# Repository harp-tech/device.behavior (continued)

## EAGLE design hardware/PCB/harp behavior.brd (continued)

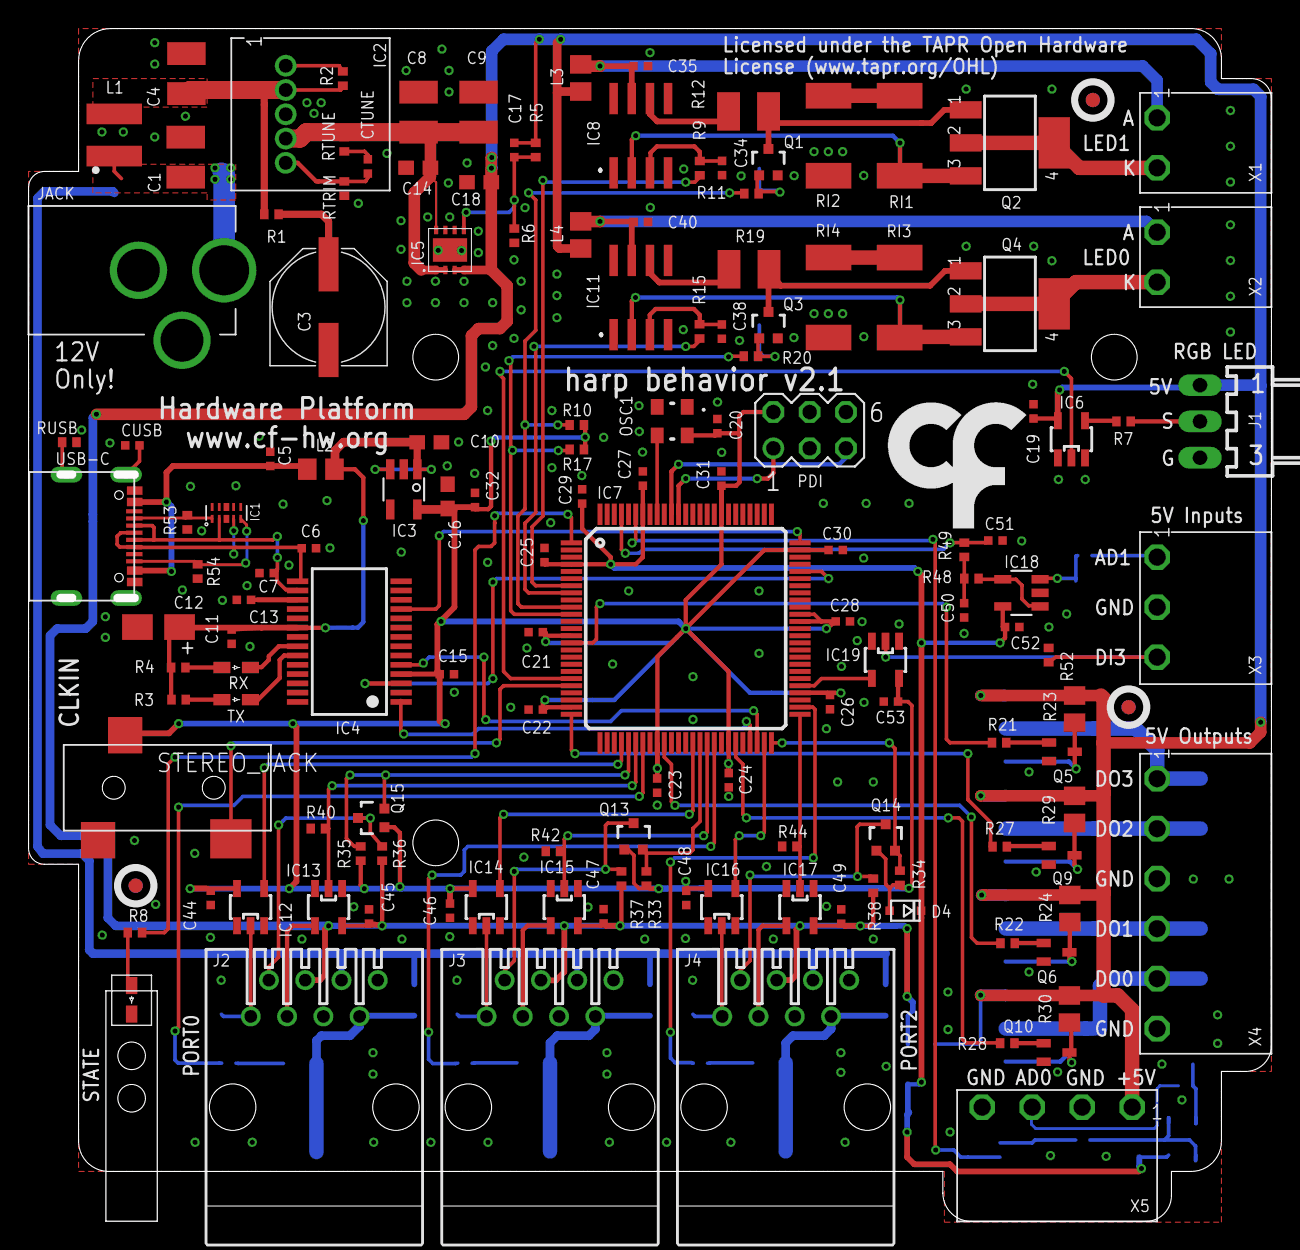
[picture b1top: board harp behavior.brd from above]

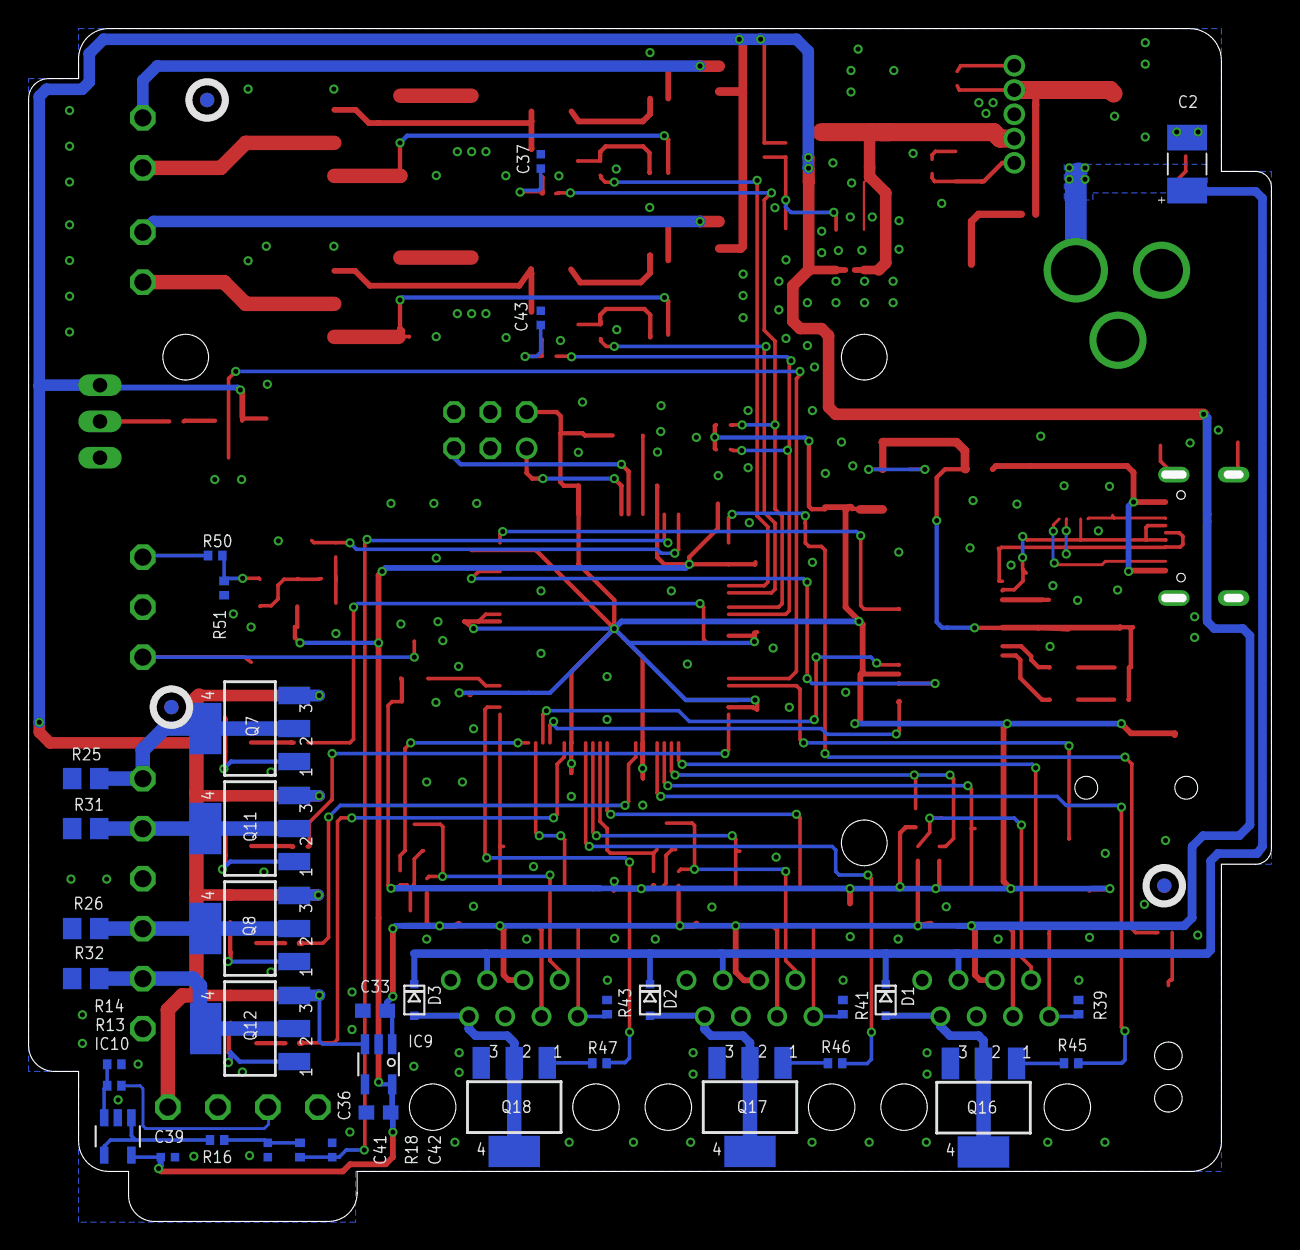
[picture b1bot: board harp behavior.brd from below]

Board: 2 copper layers, 86.4 x 82.9 mm, 186 parts (39 on the bottom side), 112 nets.

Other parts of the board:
U$1: LED_PIPE_7513D2-L
U$2, U$3, U$4, U$5, U$6, U$7: FIDUCIAL
U$9: LOGO_6

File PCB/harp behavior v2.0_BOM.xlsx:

| Part(s) | Quantity | Description | Distributor | Part. No.
 | IC1 | 1 | ESD Protection Low Cap | Mouser | 511-USBLC6-2SC6Y
 | IC2 | 1 | Conversores CC/CC sem isolação 12Vin, 0.591-6Vout 1.5A, Positive Logic | Mouser | 580-OKR-T/1.5-W12-C
 | IC3, IC9 | 2 | LDO 250mA Ultra-Lo Noise LDO Reg 3.3V | Mouser | 595-LP5907MFX-3.3NPB
 | IC4 | 1 | IC USB USB to Serial UART Enhanced IC SSOP-28 | Mouser | 895-FT232RL
 | IC5 | 1 | Reguladores de tensão de LDO Sgl Output LDO 1.5A Adj Lo Noise Hi PSRR | Mouser | 595-TPS78601DCQR
 | IC6, IC13, IC15, IC17 | 4 | Buffers e line drivers 1.65-5.5V Single Non-Inverting TTL | Mouser | 863-M74VHC1GT50DTT1G
 | IC7 | 1 | Microcontroladores de 8 bits - MCU 100TQFP, IND TEMP GREEN, 1.6-3.6V | Mouser | 556-ATXMEGA128A1U-AU
 | IC8, IC11 | 2 | Amplificadores de precisão 50MHz Low Distort Low Noise CMOS Prec | Mouser | 584-AD8651ARZ
 | IC10, IC18 | 2 | Amp Op 2.2V 50MHz Low Noise Single Supply | Mouser | 595-OPA365AIDBVR
 | IC12, IC14, IC16, IC19 | 4 | SingleBuffer / Driver, 1.65V to 5.5V, SOT-23-5 | Mouser | 595-SN74LVC1G125DBVR
 | Q1, Q3, Q13, Q14, Q15 | 5 | DMG1012UW MOSFET N Channel, 1 A, 20 V, 0.3 ohm, 4.5 V, 500 mV | Mouser | 621-DMG1012UW-7
 | Q2, Q4 | 2 | Bipolar (BJT) Single Transistor, NPN, 70 V, 150 MHz, 2 W, 2 A, 500 hFE | Mouser | 522-FZT692BTA
 | Q7, Q8, Q11, Q12 | 4 | MOSFET -60V 2.6A P-Channel SOT-223-4 | Mouser | 863-NTF2955T1G
 | Q5, Q6, Q9, Q10 | 4 | BJT NPN SURFACE MOUNT SMALL SIGNAL TRANS SOT-23-3 | Mouser | 621-BC817-40W-7
 | Q16, Q17, Q18 | 3 | MOSFET 60V 3A N-Channel SOT-223-3 | Mouser | 863-NTF3055L108T1G
 | D1, D2, D3, D4 | 4 | DIODE SCHOTTKY 30V 1A SOD323 | Mouser | 621-SDM100K30L-7
 | C17 | 1 | CAP CER 13pF 50V ±5% C0G 0402 | Mouser | 603-CC402JRNPO9BN130
 | C6, C7 | 2 | CAP CER 47pF 50V ±5% C0G 0402 | Mouser | 77-VJ0402A470JXACBC
 | CUSB | 1 | CAP CER 4.7nF 50V ±10% X7R 0402 | Mouser | 81-GCM155R71H472K37D
 | C41, C42, C50, C51 | 4 | CAP CER 15nF 16V ±10% X7R 0402 | Mouser | 581-0402YC153KAT2A
 | C5, C11, C13, C15, C19, C20, C21, C22, C23, C24, C25, C26, C27, C28, C30, C31, 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 | 29 | CAP CER 100nF 10V ±10% X5R 0402 | Farnell | 2310530
 | C29, C32 | 2 | CAP CER 330nF 10V ±10% X5R 0402 | Digikey | CL05A334KP5NNNC
 | C12 | 1 | CAP TAN 4.7uF 10V ±10% 1206 | Mouser | 80-T491A475K107280
 | C10, C14, C16, C18, C33, C36 | 6 | CAP CER 10uF 35V ±20% X5R 0603 | Mouser | 81-GRM188R6YA106MA3D
 | C2 | 1 | CAP TAN 22uF 20V ±20% 1210 | Mouser | 667-20TQC22MYFB
 | C1, C4 | 2 | CAP CER 22uF 25V ±20% X7R 1210 | Mouser | 81-GRM32ER71E226ME5K
 | C8, C9 | 2 | CAP CER 47uF 16V ±10% X6S 1210 | Mouser | 81-GRM32EC81C476KE5K
 | C3 | 1 | CAP ELE 100uF 25V ±20% E7 | Mouser | 667-25SVF100M
 | R1, R9, R15 | 3 | RES SMD 0Ω ±5% 0402 | Mouser | 667-ERJ-2GE0R00X
 | RI1, RI2, RI3, RI4 | 4 | RES SMD 4.99Ω ±1% 2512 1W | Mouser | 71-CRCW25124R99FNEG
 | R8 | 1 | RES SMD 68Ω ±5% 0402 | Mouser | 667-ERJ-2GEJ680X
 | R7, R11, R20 | 3 | RES SMD 100Ω ±1% 0402 | Mouser | 667-ERJ-2RKF1000X
 | R12, R19 | 2 | RES SMD 200Ω ±5% 1210 0.5W | Mouser | 71-CRCW1210J-200-E3
 | RTRIM | 1 | RES SMD 243Ω ±1% 0402 | Mouser | 667-ERJ-2RKF2430X
 | R45, R46, R47 | 3 | RES SMD 330Ω ±1% 0402 | Mouser | 667-ERJ-PA2F3300X
 | R16, R18, R21, R22, R27, R28, R33, R34, R35, R36, R37, R38, R48, R49 | 14 | RES SMD 10kΩ ±1% 0402 | Farnell | 2130433
 | R23, R24, R25, R26, R29, R30, R31, R32 | 8 | RES SMD 549Ω ±1% 0805 | Mouser | 667-ERJ-6ENF5490V
 | R14, R51 | 2 | RES SMD 15kΩ ±1% 0402 | Mouser | 667-ERJ-2RKF1502X
 | R13, R50 | 2 | RES SMD 24kΩ ±1% 0402 | Mouser | 667-ERJ-2RKF2402X
 | R6 | 1 | RES SMD 30.9kΩ ±1% 0402 | Mouser | 667-ERJ-2RKF3092X
 | R5 | 1 | RES SMD 95.3kΩ ±1% 0402 | Mouser | 667-ERJ-2RKF9532X
 | R10, R17, R39, R40, R41, R42, R43, R44, R52 | 9 | RES SMD 100kΩ ±1% 0402 | Mouser | 667-ERJ-2RKF1003X
 | RUSB | 1 | RES SMD 1MΩ ±1% 0402 | Mouser | ERJ-2RKF1004X
 | L1 | 1 | Indutores fixos LPS4012 Low Profile 1.5uH 2.2A 20% SMD | Mouser | 994-LPS4012-152MRB
 | L2 | 1 | Esferas de ferrite 40ohms 100MHz 1.5A Monolithic 0805 SMD | Mouser | 875-MI0805K400R-10
 | L3, L4 | 2 | Esferas de ferrite 600ohms 100MHz .5A Monolithic 0805 SMD | Mouser | 875-HZ0805E601R-10
 | STATE | 1 | SMD Pure Green 20mA 0603 | Mouser | 78-TLMP1100-GS08
 | OSC1 | 1 | Oscillator, Low Power, -40C-85C, 10ppm | Mouser | 998-1001CI5032.0000T
 | CLKIN | 1 | CONN JACK STEREO 3.5MM SMD R/A | Digikey | SC1489-1-ND
 | PDI | 1 | CONN HEADER 6POS .100 STR 15AU | Digikey | 609-3210-ND
 | J2, J3, J4 | 3 | Modular Connector, RJ45, Jack, 8 Contacts, 8 Ways, 215877 Series, Cat3 | Mouser | 571-2158771
 |  | 3 | Ethernet Cable, Patch Lead, Cat5e, RJ45 Plug to RJ45 Plug, Beige, 500 mm | Farnell | 1526101
 | USB | 1 | Conectores USB MINI B RECEPT RA TH W/POST | Mouser | UX60-MB-5S8(70)
 | USB Cable | 1 | USB Cables / IEEE 1394 Cables USB A - MINI-B 1.5M - MINI-B 1.5M BLACK | Mouser | 88732-8702
 |  | 1 | LIGHT PIPE SGL RT ANGLE 3.6MM | Digikey | L71537-ND
 | JACK | 1 | Conectores de alimentação CC PCB 2.1MM | Mouser | 163-179PH-EX
 | WALL ADAPTER | 1 | AC/DC WALL MOUNT ADAPTER 12V 12W | Mouser | VER12US120-JA
 | J1 | 1 | Connector, Right Angle, 2.54 mm, 3 Contacts, Header, KK 254 7395 Series, TH | Farnell | 22-12-4032
 |  | 2 | Pluggable Terminal Block, 3.5 mm, 2 Ways, 28 AWG, 16 AWG, 1.5 mm², Screw | Mouser | TBP03P3-350-02GR
 |  | 1 | Pluggable Terminal Block, 3.5 mm, 3 Ways, 28 AWG, 16 AWG, 1.5 mm², Screw | Farnell | 20.1550M/3-E
 |  | 2 | Pluggable Terminal Block, 3.5 mm, 6 Ways, 28 AWG, 16 AWG, 1.5 mm², Screw | Mouser | TBP03P3-350-06GR
 |  | 1 | Pluggable Terminal Block, 3.5 mm, 4 Ways, 28 AWG, 16 AWG, 1.5 mm², Screw | Farnell | 20.1550M/4-E
 | X1, X2 | 2 | Terminal Block, Header, 3.5 mm, 2 Ways, 10 A, 250 V, Through Hole Right Angle | Mouser | TBP03R1-350-02GR
 | X3 | 1 | Terminal Block, Header, 3.5 mm, 3 Ways, 10 A, 250 V, Through Hole Right Angle | Farnell | 20.155MH/3-E
 | X4 | 1 | Terminal Block, Header, 3.5 mm, 6 Ways, 10 A, 250 V, Through Hole Right Angle | Mouser | TBP03R1-350-06GR
 | X5 | 1 | Terminal Block, Header, 3.5 mm, 4 Ways, 10 A, 250 V, Through Hole Right Angle | Farnell | 20.155MH/4-E
 |  | 8 | Nut, Hex, M3, 5.5mm Nylon | RS | 525-701
 |  | 4 | Machine Screw, M3, 10 mm, Nylon (Polyamide), Pan Head Slotted | RS | 185-4447
 | Components | 191
 | Licensed under the TAPR Open Hardware License (www.tapr.org/OHL)
 | Copyright 2017-2022 Artur Silva and Filipe Carvalho
 | Licensed under the TAPR Open Hardware License (www.tapr.org/OHL)
 | Copyright 2017 Artur Silva and Filipe Carvalho

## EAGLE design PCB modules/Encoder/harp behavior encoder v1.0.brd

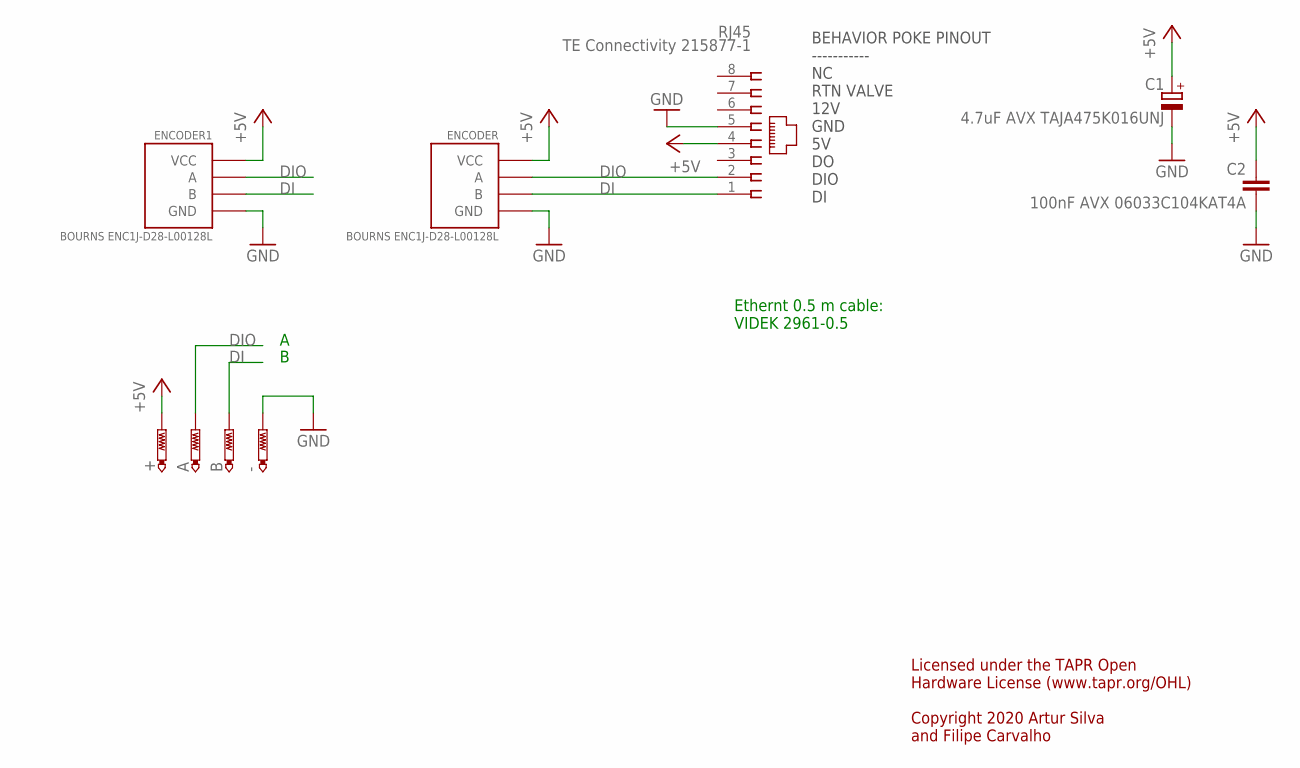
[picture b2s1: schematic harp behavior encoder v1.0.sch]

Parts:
+: PTR1PAD1-13; P1-13
-: PTR1PAD1-13; P1-13
A: PTR1PAD1-13; P1-13
B: PTR1PAD1-13; P1-13
C1: 4.7uF AVX TAJA475K016UNJ; A/3216-18W
C2: 100nF AVX 06033C104KAT4A; C0603
ENCODER, ENCODER1: BOURNS ENC1J-D28-L00128L; STYLEC
RJ45: TE Connectivity 215877-1; 520426-4

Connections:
+5V: +.TP, C1.+, C2.1, ENCODER.+ (VCC), ENCODER1.+ (VCC), RJ45.4
DI: B.TP, ENCODER.B, ENCODER1.B, RJ45.1
DIO: A.TP, ENCODER.A, ENCODER1.A, RJ45.2
GND: -.TP, C1.-, C2.2, ENCODER.- (GND), ENCODER1.- (GND), RJ45.5

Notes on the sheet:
Licensed under the TAPR Open Hardware License (www.tapr.org/OHL) Copyright 2020 Artur Silva and Filipe Carvalho
BEHAVIOR POKE PINOUT ----------- NC RTN VALVE 12V GND 5V DO DIO DI
Ethernt 0.5 m cable: VIDEK 2961-0.5

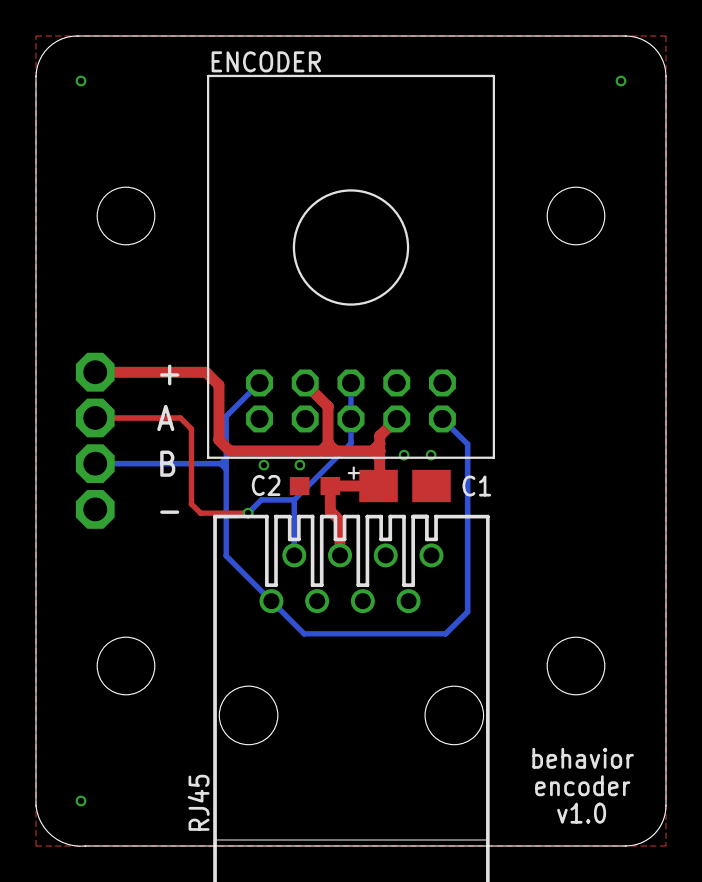
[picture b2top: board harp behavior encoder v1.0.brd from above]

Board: 2 copper layers, 35.0 x 45.0 mm, 9 parts (1 on the bottom side), 4 nets.

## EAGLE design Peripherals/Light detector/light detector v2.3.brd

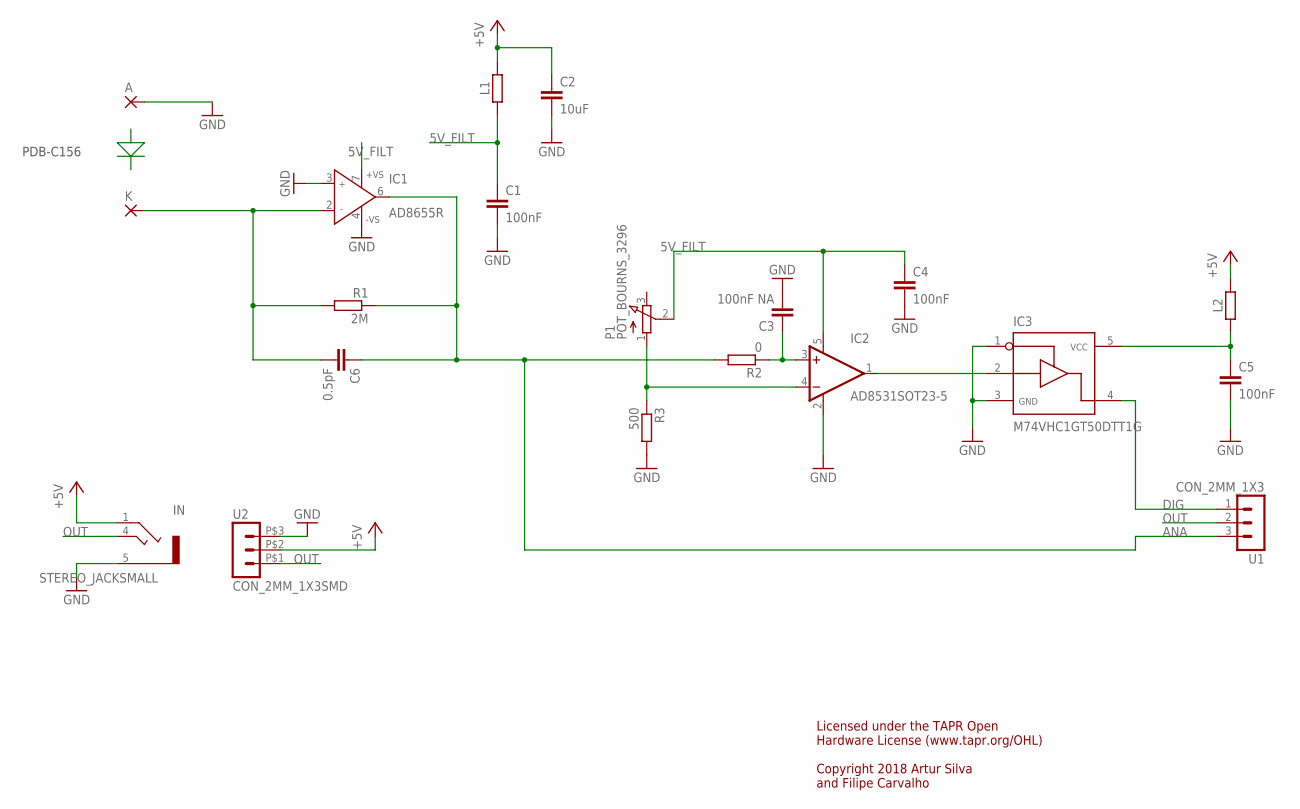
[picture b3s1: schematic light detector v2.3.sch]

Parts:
A: 1,6/0,8
C1, C4, C5: 100nF; C0402
C2: 10uF; C0603
C3: 100nF NA; C0402
C6: 0.5pF; C0402
IC1: AD8655R; SO8
IC2: AD8531SOT23-5; SOT23-5
IC3: M74VHC1GT50DTT1G; SOT23-5
IN: STEREO_JACKSMALL; 35RASMT2BHNTRX_
K: 1,6/0,8
L1, L2: 1k@100M; R0402
P1: POT_BOURNS_3296; POT_BOURNS_3296P
R1: 2M; R0402
R2: 0; R0402
R3: 500; R0402
U1: CON_2MM_1X3
U2: CON_2MM_1X3SMD; CON_2MM_1X3_SMD

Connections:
5V_FILT: C1.1, C4.1, IC1.7 (+VS), IC2.5 (V+), L1.2, P1.2 (S)
+5V: C2.1, IN.1, L1.1, L2.2, U2.P$2 (2)
ANA: C6.1, IC1.6 (OUT), R1.1, R2.2, U1.3
DIG: IC3.4, U1.1
GND: A.1, C1.2, C2.2, C3.2, C4.2, C5.2, IC1.3 (IN+), IC1.4 (-VS), IC2.2 (V-), IC3.1, IC3.3, IN.5, R3.2, U2.P$3 (3)
IN2: IC2.4 (-IN), P1.1 (A), R3.1
unnamed: C6.2, IC1.2 (IN-), K.1, R1.2
unnamed: C3.1, IC2.3 (+IN), R2.1
unnamed: IC2.1 (OUT), IC3.2
unnamed: C5.1, IC3.5, L2.1
OUT: IN.4, U1.2, U2.P$1 (1)

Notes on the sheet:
Licensed under the TAPR Open Hardware License (www.tapr.org/OHL) Copyright 2018 Artur Silva and Filipe Carvalho
PDB-C156

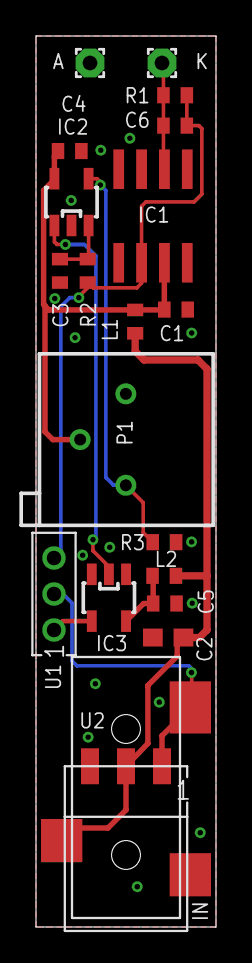
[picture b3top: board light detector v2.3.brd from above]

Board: 2 copper layers, 10.0 x 49.5 mm, 21 parts (1 on the bottom side), 11 nets.

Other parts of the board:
U$2: LOGO_8

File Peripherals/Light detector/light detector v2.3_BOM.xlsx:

| Part(s) | Quantity | Description | Distributor | Part. No.
 | IC1 | 1 | IC OPAMP GP 28MHZ RRO 8SOIC | Digikey | AD8655ARZ-REEL7CT-ND
 | IC2 | 1 | IC OPAMP GP 3MHZ RRO SC70-5 | Digikey | AD8531ARTZ-REEL7
 | IC3 | 1 | Buffers e line drivers 1.65-5.5V Single Non-Inverting TTL | Digikey | M74VHC1GT50DTT1GOSCT-ND
 | P1 | 1 | TRIMMER 20K OHM 0.5W PC PIN | Digikey | 3296P-203LF-ND
 | R2 | 1 | RES SMD 0 OHM JUMPER 1/10W 0402 | Digikey | P0.0JCT-ND
 | R3 | 1 | RES SMD 499 OHM 1% 1/10W 0402 | Digikey | P499LCT-ND
 | R1 | 1 | RES SMD 2000K OHM 1% 1/10W 0402 | Digikey | ERJ-2GEJ205X
 | C6 | 1 | CAP CER 0.5PF 50V C0G/NP0 0402 | Digikey | 490-6264-1-ND
 | C1, C4, C5 | 3 | CAP CER 100nF 10V X5R 0402 | REEL | REEL
 | C2 | 1 | CAP CER 10uF 10V ±10% X5R 0603 | Digikey | 490-10474-1-ND
 | L1, L2 | 2 | FERRITE BEAD 1 KOHM 0402 1LN | Digikey | 445-2163-1-ND
 | U1 | 1 | CONN HEADER R/A 3POS 2MM | Digikey | M22-2030305
 | U2 | 0 | CONN RCPT 2MM SMD 3POS | Digikey | 952-3182-2-ND
 | Jumper | 1 | CONN JUMPER SHORTING GOLD BLACK | Digikey | M22-1900005
 | IN | 1 | SMT 3.5 STEREO REEL | Digikey | 502-35RASMT2BHNTRX
 |  | 1 | CABLE 3.5MM STEREO PLUG W/WIRES | Digikey | 1847-BC-A3ML006F-ND
 | Sensor | 1 | PHOTODIODE BLUE 8.02MM SQ CLEAR | Digikey | PDB-C156-ND
 | Components | 19
 | Licensed under the TAPR Open Hardware License (www.tapr.org/OHL)
 | Copyright 2018 Artur Silva and Filipe Carvalho

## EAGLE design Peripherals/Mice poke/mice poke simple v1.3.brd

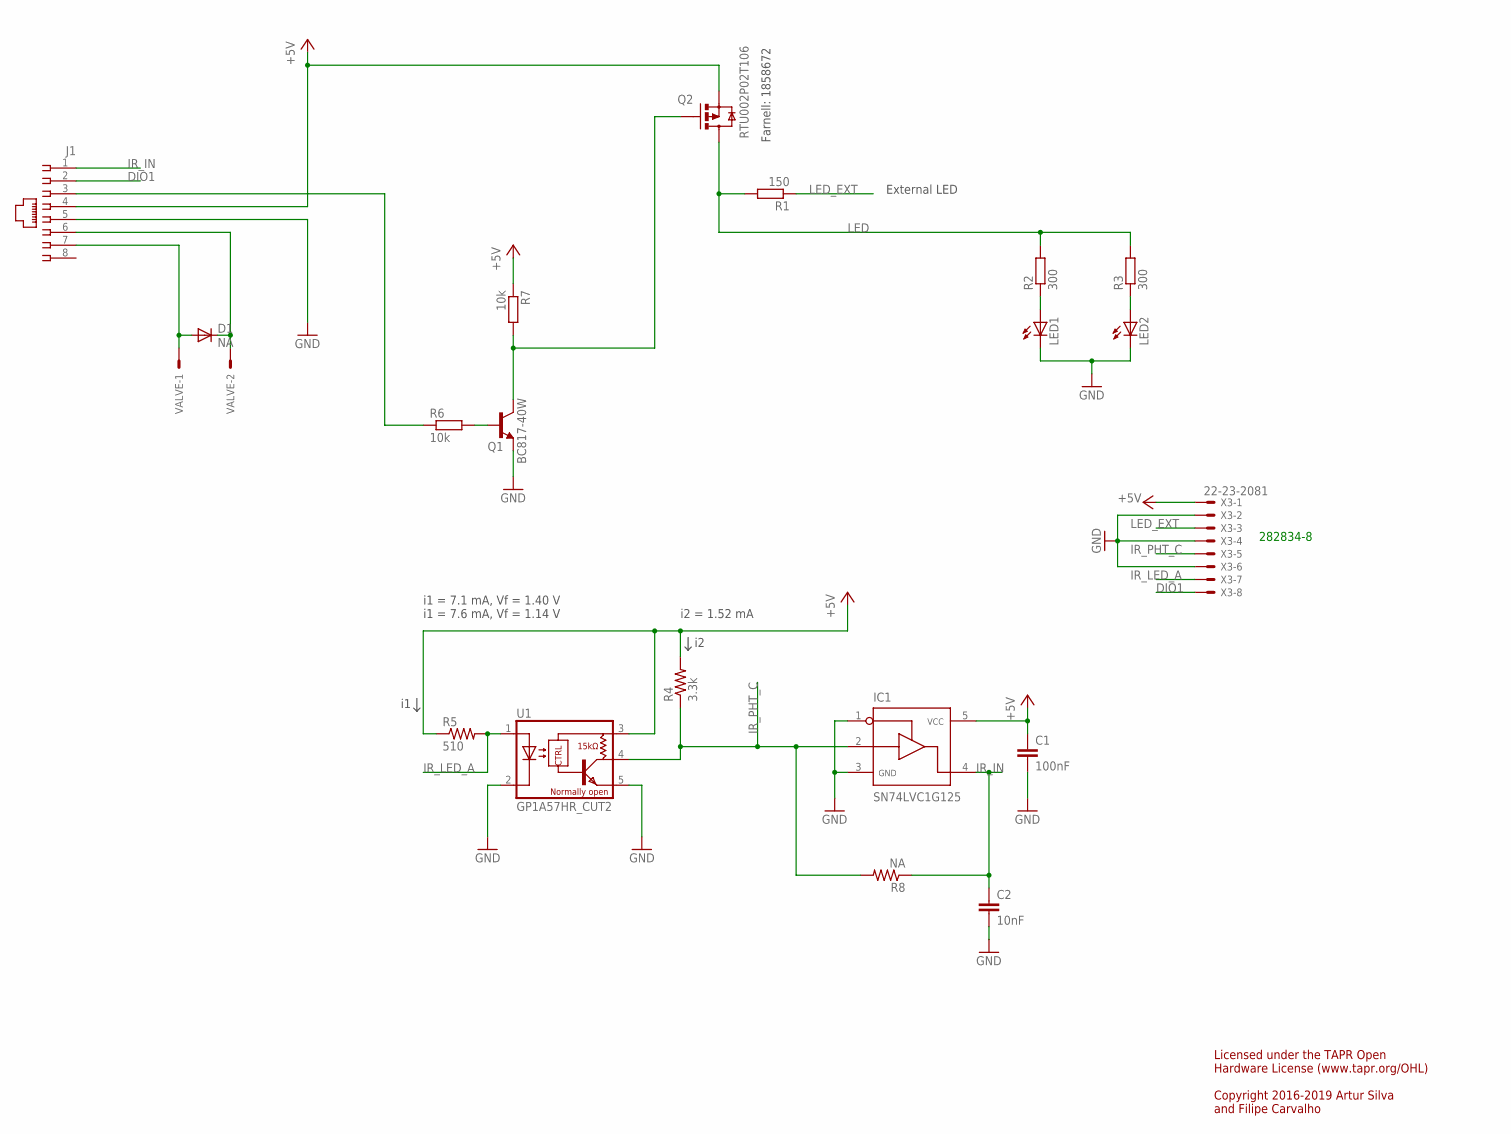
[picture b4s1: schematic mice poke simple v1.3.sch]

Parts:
C1: 100nF; C0402
C2: 10nF; C0402
D1: NA; SOD323-R
IC1: SN74LVC1G125; SOT23-5
J1: 215878-2
LED1, LED2: LED3MM
Q1: BC817-40W; SOT323-BEC
Q2: RTU002P02T106; SOT323
R1: 150; R0402
R2, R3: 300; R0402
R4: 3.3k; R0402
R5: 510; R0402
R6, R7: 10k; R0402
R8: NA; R0402
U1: GP1A57HR_CUT2
VALVE: 22-23-2021
X3: 22-23-2081

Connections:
+5V: C1.1, IC1.5, J1.4, Q2.1 (S), R4.2, R5.1, R7.1, U1.3 (VCC), X3.1
DIO1: J1.2, X3.8
GND: C1.2, C2.2, IC1.1, IC1.3, J1.5, LED1.K (C), LED2.K (C), Q1.E, U1.2 (C), U1.5 (GND), X3.2, X3.4, X3.6
IR_IN: C2.1, IC1.4, J1.1, R8.1
IR_LED_A: R5.2, U1.1 (A), X3.7
IR_PHT_C: IC1.2, R4.1, R8.2, U1.4 (VO), X3.5
LED: Q2.3 (D), R1.2, R2.2, R3.2
LED_EXT: R1.1, X3.3
unnamed: D1.A, J1.7, VALVE.1
unnamed: D1.C, J1.6, VALVE.2
unnamed: J1.3, R6.1
unnamed: LED2.A, R3.1
unnamed: LED1.A, R2.1
unnamed: Q1.C, Q2.2 (G), R7.2
unnamed: Q1.B, R6.2

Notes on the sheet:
i1 = 7.1 mA, Vf = 1.40 V i1 = 7.6 mA, Vf = 1.14 V
i2 = 1.52 mA
External LED
Farnell: 1858672
Licensed under the TAPR Open Hardware License (www.tapr.org/OHL) Copyright 2016-2019 Artur Silva and Filipe Carvalho
282834-8

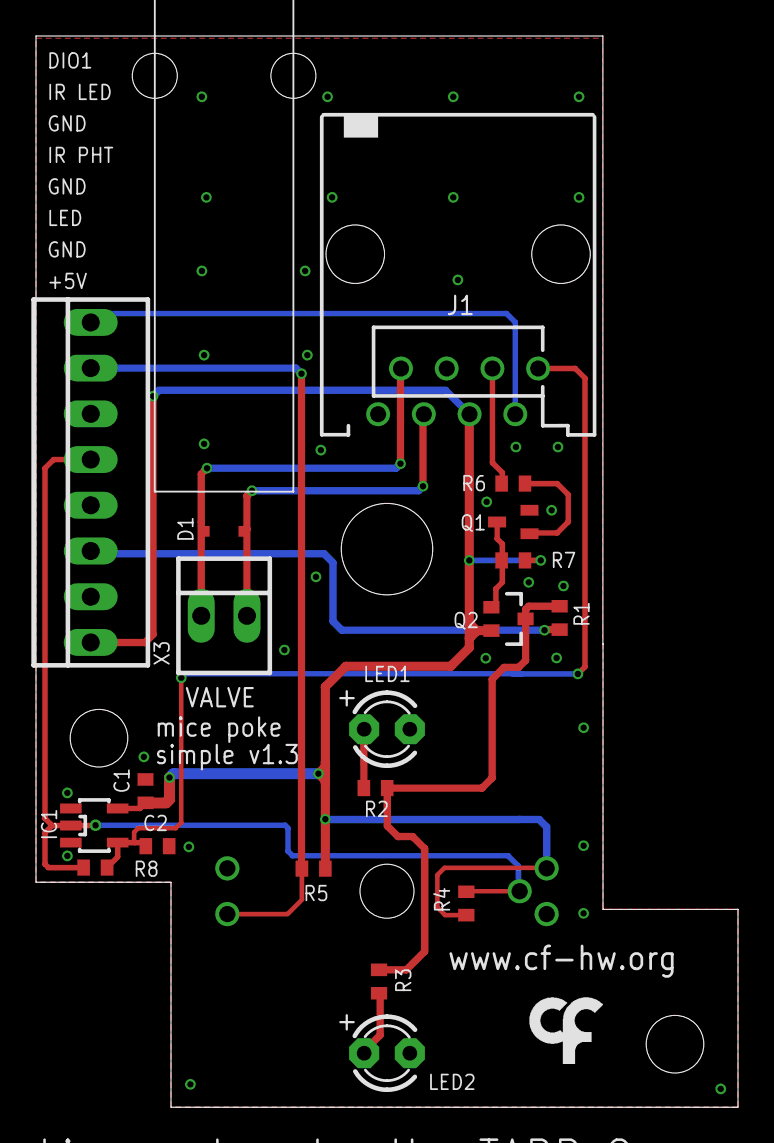
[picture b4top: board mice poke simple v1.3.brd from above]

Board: 2 copper layers, 39.0 x 59.5 mm, 21 parts (1 on the bottom side), 15 nets.

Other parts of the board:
U$2: LOGO_7

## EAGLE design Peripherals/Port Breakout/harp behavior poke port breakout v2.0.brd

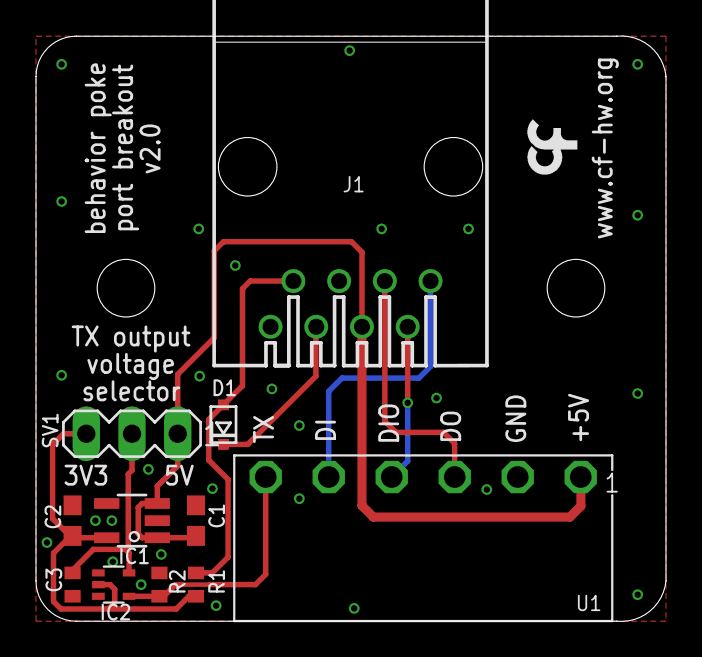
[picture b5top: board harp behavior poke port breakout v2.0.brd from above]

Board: 2 copper layers, 35.0 x 32.5 mm, 12 parts (0 on the bottom side), 10 nets.

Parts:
C1, C2: 4.7uF; C0603
C3: 100nF; C0402
D1: SOD-323-DIODE
IC1: TLV70033DDCR; TSOT23-5
IC2: 74AHC1G04DCK; SC70-5
J1: Port 1; 520426-4
R1: 1k; R0402
R2: 100k; R0402
SV1: MA03-1
U1: CON_3.5MM_1X6
U$2: LOGO_8

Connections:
+3V3: C2.1, IC1.5, IC2.2, R1.1, SV1.3
+5V: C1.1, IC1.1, IC1.3, J1.4, SV1.1, U1.P1
+12V: D1.C, J1.6
DI: J1.1, U1.P5
DIO: J1.2, U1.P4
DO: J1.3, U1.P3
GND: C1.2, C2.2, C3.1, IC1.2, IC2.3, J1.5, R2.2, U1.P2
unnamed: C3.2, IC2.5, SV1.2
SUP_RTN: D1.A, J1.7, R1.2
TX: IC2.4, R2.1, U1.P6

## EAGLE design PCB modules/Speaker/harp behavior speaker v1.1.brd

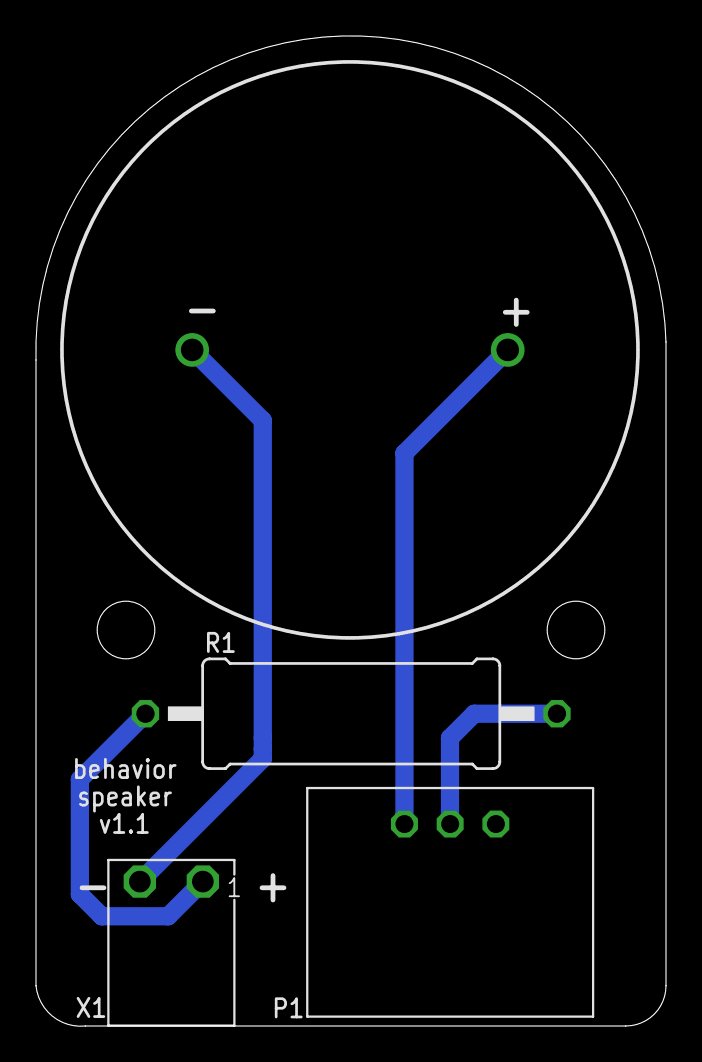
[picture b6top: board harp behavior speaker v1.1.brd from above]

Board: 2 copper layers, 35.0 x 55.0 mm, 3 parts (0 on the bottom side), 2 nets.

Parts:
P1: 91A1A-B28; MODEL91
R1: 24; 0617/22
X1: CON_3.5MM_1X2

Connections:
unnamed: R1.1, X1.P1
unnamed: P1.P$2, R1.2

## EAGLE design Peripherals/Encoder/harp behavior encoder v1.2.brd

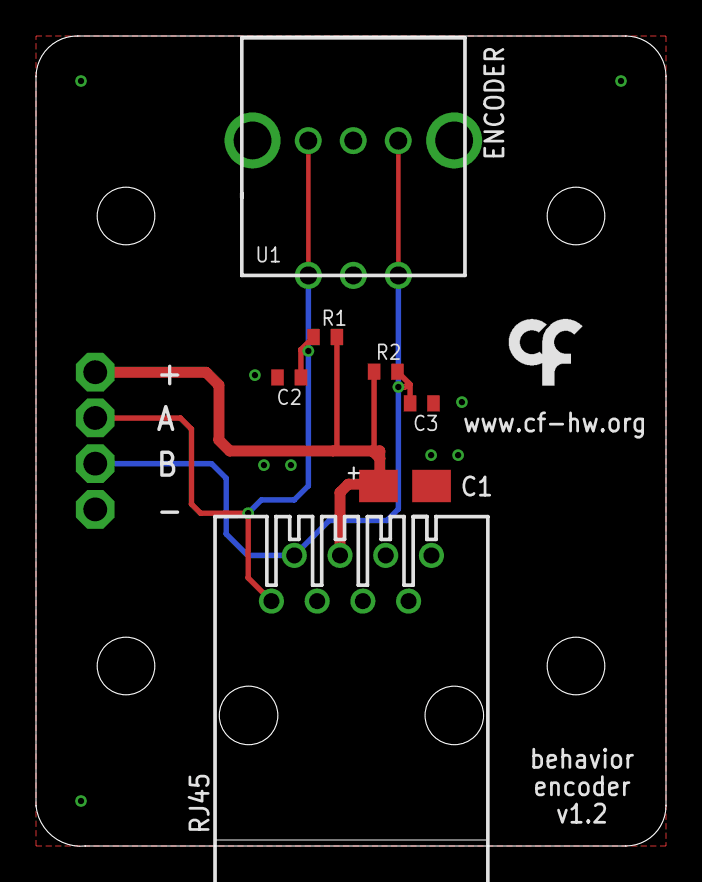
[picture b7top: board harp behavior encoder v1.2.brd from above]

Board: 2 copper layers, 35.0 x 45.0 mm, 12 parts (0 on the bottom side), 4 nets.

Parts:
+: PTR1PAD1-13; P1-13
-: PTR1PAD1-13; P1-13
A: PTR1PAD1-13; P1-13
B: PTR1PAD1-13; P1-13
C1: 4.7uF AVX TAJA475K016UNJ; A/3216-18W
C2, C3: 100nF; C0402
R1, R2: 10k; R0402
RJ45: TE Connectivity 215877-1; 520426-4
U1: ENCODER_EC12
U$3: LOGO_7

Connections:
+5V: +.TP, C1.+, R1.1, R2.1, RJ45.4
DI: A.TP, C2.1, R1.2, RJ45.1, U1.A
DIO: B.TP, C3.1, R2.2, RJ45.2, U1.B
GND: -.TP, C1.-, C2.2, C3.2, RJ45.5, U1.C

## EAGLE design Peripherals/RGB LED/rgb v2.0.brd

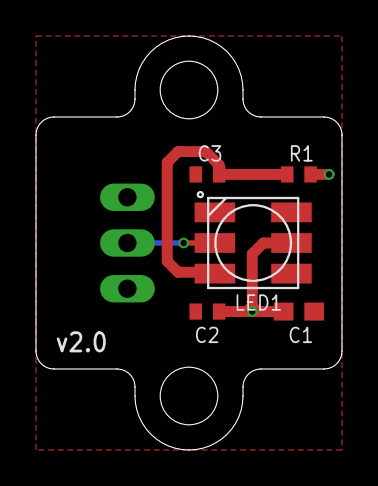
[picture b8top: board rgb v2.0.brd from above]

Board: 2 copper layers, 17.0 x 23.0 mm, 6 parts (1 on the bottom side), 4 nets.

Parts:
C1: 10uF; C0603
C2, C3: 100nF; C0402
J1: 22-05-7038-03; 7395-03
LED1: WS2812LARGER; WS2812_LARGER
R1: 33; R0402

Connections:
+5V: C1.1, C2.1, J1.1, LED1.LEDVDD, R1.2
GND: C1.2, C2.2, C3.2, J1.3, LED1.VSS
unnamed: C3.1, LED1.VDD, R1.1
SERIAL_LED0: J1.2, LED1.DI

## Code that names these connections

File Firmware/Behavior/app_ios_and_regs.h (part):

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/* Registers' address                                                   */
/************************************************************************/
/* Registers */
#define ADD_REG_PORT_DIS                    32 // U8     Reflects the state of DI digital lines of each Port
#define ADD_REG_RESERVED0                   33 // U8     Reserved for future use
#define ADD_REG_OUTPUTS_SET                 34 // U16    Set the correspondent output
#define ADD_REG_OUTPUTS_CLEAR               35 // U16    Clear the correspondent output
#define ADD_REG_OUTPUTS_TOGGLE              36 // U16    Toggle the correspondent output
#define ADD_REG_OUTPUTS_OUT                 37 // U16    Control the correspondent output
#define ADD_REG_PORT_DIOS_SET               38 // U8     Set the correspondent DIO
#define ADD_REG_PORT_DIOS_CLEAR             39 // U8     Clear the correspondent DIO
#define ADD_REG_PORT_DIOS_TOGGLE            40 // U8     Toggle the correspondent DIO
#define ADD_REG_PORT_DIOS_OUT               41 // U8     Control the correspondent DIO
#define ADD_REG_PORT_DIOS_CONF              42 // U8     Set the DIOs direction (1 is output)
#define ADD_REG_PORT_DIOS_IN                43 // U8     State of the DIOs
#define ADD_REG_DATA                        44 // I16[2] Voltage at ADC input and decoder (poke 2) value
#define REG_DATA_INDEX_ADC0						0	// Index for the value of ADC0
#define REG_DATA_INDEX_ADC1						1   // Index for the value of ADC1
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#define MSK_MIMIC                          0x0F         // 
#define GM_MIMIC_NONE                      0x00         // 
#define GM_MIMIC_DIO0                      0x01         // Is reflected on DIO0
#define GM_MIMIC_DIO1                      0x02         // Is reflected on DIO1
#define GM_MIMIC_DIO2                      0x03         // Is reflected on DIO2
#define GM_MIMIC_DO0                       0x04         // Is reflected on DO0
#define GM_MIMIC_DO1                       0x05         // Is reflected on DO1
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
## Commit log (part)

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2017-11-24 Added hability to change the DOx frquency and Duty Cycle when already operating the DOx outputs.
2017-11-24 Negated LEDs transistor drive and added new bit to be used on register PWM_START.
2017-11-24 Added pulse functionality and clean some registers.
2017-11-24 Added pulse functionality, shutdown in case of error, correct DAC initialization, changed some register defaults and added some register initializations.
2017-11-24 Minor changes on file registers.xls.
2017-11-25 Removed unnecessary library.
2017-11-25 Fixed the ADC conversion.
2017-11-25 Increased ADC stabilization time before measuring offset from 5 us to 100 us (doesn't have impact on the offset value).
2017-11-26 Improved RGB control, changed RGB defaults and clean up code.
2018-01-11 Fixed #1.
2018-01-11 Updated to Atxmega Harp core version 1.1.
2018-01-11 Increased firmware version to 1.1
2018-01-12 Updated hwbp_app_initialize function to make it easy for the releases.
2018-01-17 Fixed Rgbs issue where the high level interrupts were interrupting the RGB bus and creating erroneous colors. Note: Not sure if completely fixed -- the Clock Sync's uart can still create interruption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
2018-01-17 Added code to keep the register OUTPUTS_OUT constantly updated.
2018-01-29 Updated to Atxmega Harp core version 1.3.
2018-01-31 Updated to Atxmega Harp core version 1.4.
2018-02-23 Added new registers and implemented quadrature encoder register's code.
2018-02-23 Increased firmware version to 2.0.
2018-03-01 Implemented 3 new features (camera controller, quadrature counter, servo motor controller) and renamed/removed some registers.
2018-03-02 Deleted the register DIS_ENCODERS.
2018-03-02 Fixed issue that was creating a bad frequency when updating the frequency registeres during PWM execution.
2018-03-02 Fixed issue. The stop pwm of channel 1, 2 and 3 was not operational.
2018-03-02 Fixed issue that was turning the cameras off after the pulse period.
2018-03-04 Reordered the GRB array of colors to RGB.
2018-03-04 Increased lower limit of the camera frequency to 2 Hz (1 Hz was not working properly).
2018-03-04 Corrected return values when writing to some registers.
2018-03-04 Ability to update the quadrature counter value.
2018-03-04 Added new feature: servo motor is enabled when the pwm pulse registers are updated.
2018-03-04 Updated the registers default list.
2018-03-04 Removed old ADC register from the default values list.
2018-03-14 Corrected issue: when stopping the camera triggering, the last pulse was not correct.
2018-03-14 Increased firmware version to 2.1.
2018-04-27 Added filter to the PORTx digital inputs.
2018-04-27 Increased firmware version to 2.2.
2018-12-14 Reduced analog input conversion to 1 KHz.
2019-01-03 Updated hardware version to the latest version available.
2019-01-03 Updated firmware version to 2.3. Needed to overcome some preliminary versions 2.2 released for tests..
2019-01-10 Correct events from cameras triggering.
2019-02-06 Updated to core version 1.5 and use new ADC routines for the analog reading.
2019-02-11 Updated to core version 1.6.
2019-12-04 Added ability to mimic the infrared beams and valves into the outputs.
2020-05-24 Added fabrication files.
2021-11-03 Added license files
2022-01-22 Implemented a low-pass filter for the Pokes' digital input
2022-01-22 Increased firmware version
2022-03-17 Upadate registers.xls with new input filter register and update metadata
2022-03-17 Add low pass filter register missing on app_funcs.h from previous release (v2.6)
2022-03-17 Configure pokes DIOs as inputs, add respective events and increase version
2022-03-17 Correct hw version of release v2.6 file and add release v2.5
2022-03-17 Update project version to v7.0 and add v6.2 compatible version files
2022-05-20 Updated to harp core v1.10
2022-05-20 Added ability to calculate ADC offset and read ADC1.
    The devices is now able to calculate its own ADC offset and apply it to ADC readings.
    ADC readings are now handled by interrupts.
    Reading of ADC1 is done for hardware version 2.0.
2022-05-21 Updated LICENSE date.
2022-05-26 Implemented digital input DI3 on firmware.
2022-07-01 Harp behavior v2.0 hardware CAD files
2022-07-01 Revert "Harp behavior v2.0 hardware CAD files"
    This reverts commit b7fb75ff22a1f2c396da8856b179b4330b59d1a1.
2022-07-06 Added firmware image files.
2022-08-04 Added fw release 2.7 .hex file
2022-08-30 Updated README.md.
2022-09-13 Added a new event, when the last trigger is sent to the camera.
2022-09-16 Correct files added
2022-09-16 Organize folders and add peripheral boards
2022-09-16 License files added
2022-09-21 Organized files for PCB version 1.2.
2022-09-21 Added the available peripherals.
2022-09-21 Added PCB version 2.0.
2022-09-22 Added device's photo.
2022-10-05 Added port breakout v2.0.
2022-10-05 Minor corrections.
2022-10-05 Added production files.
2022-11-25 Added port breakout v2.1.
2022-11-30 Added BOM for v2.0 and updated CONTRIB file
2022-12-09 Updated port breakout v2.1
2022-12-23 refactor repository structure
2022-12-27 Added specific .gitignore for Hardware.
2022-12-27 Organized files for PCB version 2.0.
2022-12-27 Removed Releases folder from Firmware.
    Firmware will be found under repository releases from now on.
2022-12-27 Added specific .gitignore for Firmware.
2022-12-27 Created registers and control bits.
2022-12-27 Implemented the new functionality.
    Implements the ability to send the current timestamp over serial on Port 2, using the Valve line.
2022-12-27 Released fw 3.1 with atxmega harp core 1.11
2023-01-25 Correct mechanical version v1.x
2023-01-25 Add mechanical files v2.0 and License
2023-03-23 Add prototype device schema and interface
2023-03-27 Regenerate high-level device interface
2023-03-28 Add interface license and fix description
2023-03-29 Generate symbols package
2023-06-06 Add second ADC channel to schema
2023-06-06 Update `Device` class to the new schema
2023-06-06 Increment patch version
2023-06-07 Change AnalogData payloadSpec name
2023-06-07 Update `Device` class
2023-06-28 Fix register mask reference
2023-06-28 Refactor DigitalInput register naming
2023-07-31 Update interface to use new generators
2023-08-03 Add missing package metadata for stable release
2023-08-10 Updated versions.
2023-08-10 Replaced harp core 1.11 with 1.13.
2023-08-31 Raised version.
2023-08-31 Created new register EncoderMode.
2023-08-31 Implemented the functionality.
2023-08-31 Fixed core initialization.
2023-08-31 Added register description.
2023-09-06 Adding register limits
2023-09-18 Change encoder mode register and mask name
2023-11-19 Update interface to emit new encoder mode register
2023-11-19 Update interface to emit private registers
2024-04-18 Include device metadata file as embedded resource
2024-04-18 Add operator to retrieve embedded device metadata
2024-05-02 Document `Event` access for CameraStop register
2024-05-06 Document Event feature
2024-09-29 Fix register access description
2024-11-01 Update default launch settings
2024-11-07 Update generators to use embedded device metadata
2024-11-09 Add library package type to interface project
2024-11-16 Add CI to check for uncommitted changes during the regeneration process
2025-02-01 Add operator to convert raw adc units to volt
2025-02-01 Fix adc to voltage conversion
2025-02-01 Fix minor typo
2025-05-24 Update interface using new generators
2025-05-24 Remove unused csproj properties and copyright date
2025-05-24 Add global.json for reproducible builds
2025-05-24 Add README file to device package
2025-05-27 Add example of async API to demonstrate C# usage
2025-05-27 Update version to avoid skipping a release
2025-06-12 Create basic CI/CD for interface package
2025-07-09 Testing different layouts
2025-07-14 Update device yaml file to support 3 encoders
2025-07-21 Digital Outputs Start and Stop PWM buttons added
2025-07-21 Toggle buttons at the PWMs implemented
2025-07-21 Update firmware to support 3 encoders Separate analog and encoder data into separate registers
2025-07-25 New tab item tested out
2025-07-25 Display Inputs
2025-07-28 new configuration
2025-07-29 Added Apply buttons for RGBs LEDs and DOs
2025-07-29 Redesign of analog input
2025-07-29 Added events tab
2025-07-29 Deleted extra commands in operations
2025-07-30 Apply specific buttons to the extended features
2025-07-31 Added input/output direction combo box for the DIOs
2025-07-31 PORT 1 stack completed with black boxes
2025-08-01 Grid completed
2025-08-01 Added a review view of the DIs and corrected some typos
2025-08-01 Added apply button at the timestamp
2025-08-06 Set and Clear Buttons were made interactive @ DIOs and @ RGBs and LEDs
2025-08-08 Added same configuration and table view to every tab, added button apply specific to DIOs pulse configuration
2025-08-08 Added remining Apply buttons
2025-08-13 Improved view for the mimic control cells
2025-08-13 RGBs and LEDs: made the set and clear interactive; corrected apply buttons; added button for the current control and the color control
2025-08-13 Advanced Controls: same width for the 1st column
2025-08-13 Made the start and stop buttons intetactive as well as then enable and disable
2025-09-03 Fix read digital inputs function on firmware
2025-09-16 Reviewed servo motors outlook at the remake tab in the view
2025-09-16 corrected distance at apply button in the servos
2025-09-16 open tab is the second
2025-09-16 Enable/disable button fit the screen
2025-09-16 Corrected typo
2025-09-16 removed duplicated advanced controls
2025-09-16 corrected labels at ports
2025-09-16 corrected limits current of leds
2025-09-16 changed label of timesatmp
2025-09-16 Added digital input on the di/os tab
2025-09-16 Cleaned up the viewmodel: unsured functions and commands
2025-09-16 clean up view model
2025-09-16 Corrected identation at the view document
2025-09-16 Added comprehensive labels on the view
2025-09-16 corrected frame acquired active camera binding states
2025-09-16 updaated readme
2025-09-16 Corrections applied on the xmal file - improve readibility of the file Added read me onto the the 'app' directory
2025-09-16 prepare for executable of different architectures
2025-09-16 added teh direction input apply button
2025-09-16 deleted unused functionalities
2025-10-21 Updated core to version 1.15
2025-10-22 Raise fw version to v3.3
2025-10-24 Update fw version device.yml (#34)
2026-02-11 Remove BOM from generated interface file
    This avoids conflict with CI/CD pipeline. In the future we may want to
    remove the BOM from all source files.
2026-03-17 Regenerate interface using harp toolkit
    The latest release of harp toolkit deprecates the legacy Generators
    project.
    T4 templates are also pre-compiled meaning there is no need to install
    dotnet-t4.
2026-03-22 Adopt naming convention for mask suffix
    This allows removing redundant words from firmware definition names.
    The version of the generators is also updated bringing minor
    improvements to interface documentation wording.
2026-05-05 Use description attribute for encoder tooltips
2026-05-05 Declare DataType on enum display template
    Declaring an explicit type on the shared EnumDisplayTemplate allows the
    Avalonia compiler to validate the binding under compiled bindings
    without relying on inference from the surrounding ItemsControl.
2026-05-05 Fix nullable warnings
2026-05-05 Read tooltip text from description attribute
2026-05-05 Remove unused package readme
2026-05-05 Rename view model source files to match class name
2026-05-05 Update app logos and org statements
    Includes all harp logo variants. As the logo works equally well in light
    and dark themes, we also remove the theme variant scopes.
    Ensure harp-tech org statements are consistent with other repository
    components. Contributing statements are temporarily removed to make
    room for an org-level CONTRIBUTING.md file.
